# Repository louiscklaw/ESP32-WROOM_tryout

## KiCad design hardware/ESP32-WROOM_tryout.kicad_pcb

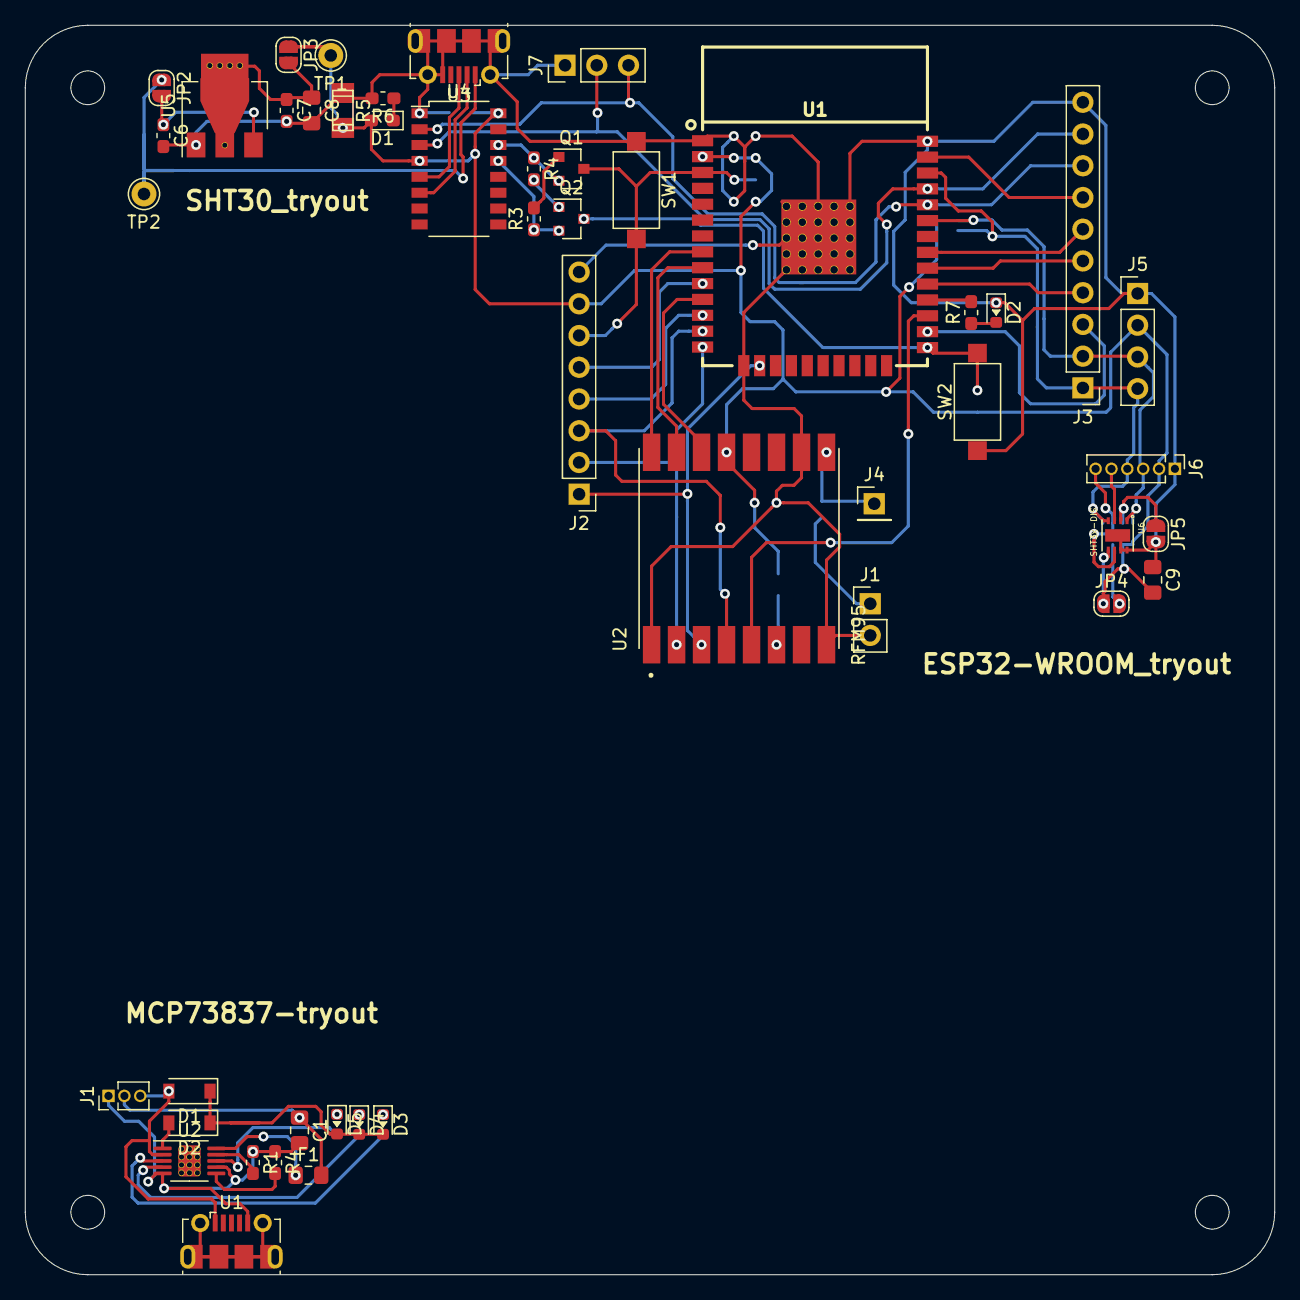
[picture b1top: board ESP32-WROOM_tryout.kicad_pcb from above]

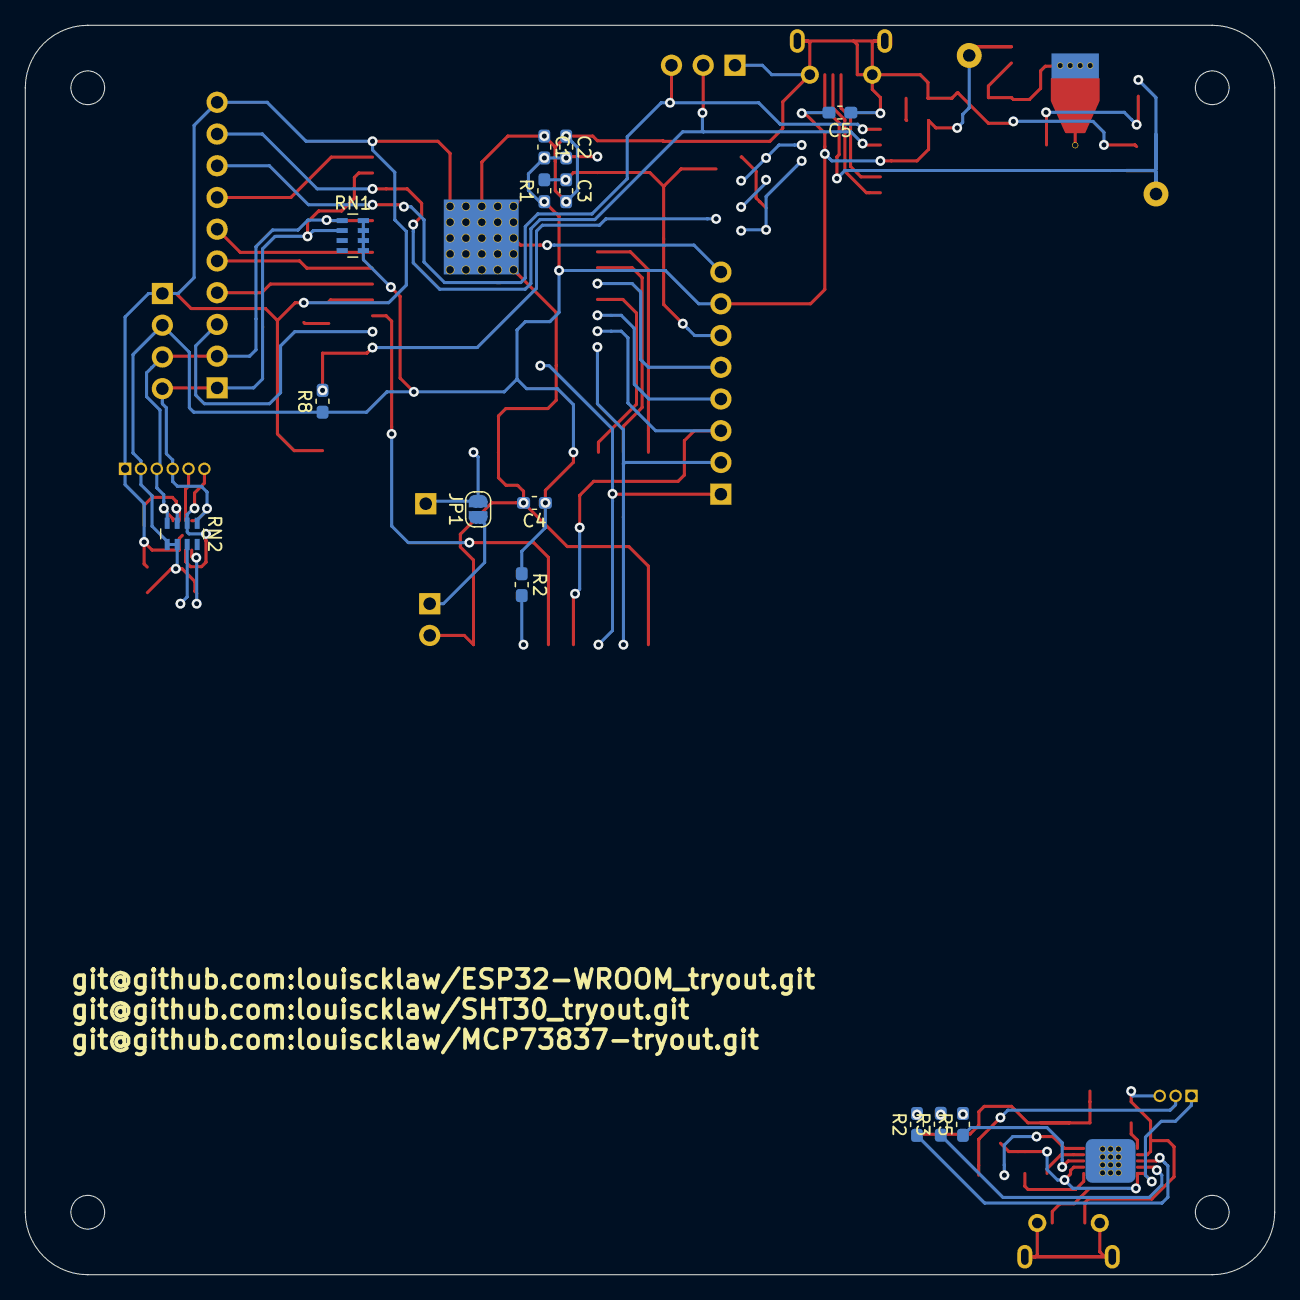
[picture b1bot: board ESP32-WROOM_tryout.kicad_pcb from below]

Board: 2 copper layers, 100.0 x 100.0 mm, 64 parts (14 on the bottom side), 51 nets.

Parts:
C1, C8: C106,0805; C_0805_2012Metric_Pad1.15x1.40mm_HandSolder
C1#2: C106,0603; C_0603_1608Metric_Pad1.05x0.95mm_HandSolder
C2, C3, C5, C6, C7: C104,0603; C_0603_1608Metric_Pad1.05x0.95mm_HandSolder
C4: C475,0603; C_0603_1608Metric_Pad1.05x0.95mm_HandSolder
C9: C104,0805; C_0805_2012Metric_Pad1.15x1.40mm_HandSolder
D1, D2: D_1N4148_T4; D_SOD-123
D1#2: LED_GREEN,0603; LED_0603_1608Metric_Pad1.05x0.95mm_HandSolder
D2#2: LED_BLUE,0603; LED_0603_1608Metric
D3: LED_ORANGE,0603; LED_0603_1608Metric
D4: LED_GREEN,0603; LED_0603_1608Metric
D5: LED_RED,0603; LED_0603_1608Metric
F1: Fuse_Small,0805; R_0805_2012Metric_Pad1.15x1.40mm_HandSolder
H1, H2, H3, H4: MOUNT_M2.5; MountingHole_2.7mm_M2.5,rpi_like
J1: OUT_HEADER; PinHeader_1x03_P1.27mm_Vertical
J1#2: ANT; PinHeader_1x02_P2.54mm_Vertical
J2: HEADER1; PinHeader_1x08_P2.54mm_Vertical
J3: HEADER2; PinHeader_1x10_P2.54mm_Vertical
J4: ANT; PinHeader_1x01_P2.54mm_Vertical
J5: I2C_HEADER; PinHeader_1x04_P2.54mm_Vertical
J6: SHT3x_HEADER; PinHeader_1x06_P1.27mm_Vertical
J7: TTL_DEBUG; PinHeader_1x03_P2.54mm_Vertical
JP1: ANT_EN; SolderJumper-2_P1.3mm_Open_RoundedPad1.0x1.5mm
JP2: 5V_EN; SolderJumper-2_P1.3mm_Open_RoundedPad1.0x1.5mm
JP3: 3V3_EN; SolderJumper-2_P1.3mm_Open_RoundedPad1.0x1.5mm
JP4: SolderJumper_2_Open_round; SolderJumper-2_P1.3mm_Open_RoundedPad1.0x1.5mm
JP5: J_ADDR; SolderJumper-2_P1.3mm_Open_RoundedPad1.0x1.5mm
Q1, Q2: 2N3904(1AM); MBT3904_1AM_SOT
R1, R1#2, R2, R3, R4, R7, R8: R103,0603; R_0603_1608Metric_Pad1.05x0.95mm_HandSolder
R2#2, R3#2, R4#2, R5: R122,0603; R_0603_1608Metric_Pad1.05x0.95mm_HandSolder
R5#2: VAR_3V3,1206; VAR_1206
R6: R102,0603; R_0603_1608Metric_Pad1.05x0.95mm_HandSolder
RN1: RN_473,0603; R_Array_Concave_4x0603
RN2: RN_472,0603; R_Array_Concave_4x0603
SW1, SW2: SW_RESET,2_leg,SMD; SW_SPST_CK_RS282G05A3
TP1: TP_3V3; Pin_D1.0mm_L10.0mm
TP2: TP_5V; Pin_D1.0mm_L10.0mm
U1, U3: USB_Micro; USB_Micro-B_Molex-105017-0001
U1#2: ESP-WROOM-32NARROW
U2: MCP73837_MSOP10
U2#2: RFM95
U4: CH340C
U5: AMS1117-3.3; AMS1117_SOT-223
U6: SHT3x-DIS

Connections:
+3V3: C1#2.2, C2.2, C4.1, C5.2, C9.2, D1#2.2, J2.7, J5.2, J6.2, JP3.1, JP4.1, R1.1, R2.1, R5#2.1, R8.1, RN1.5, RN1.6, RN1.7, RN1.8, RN2.5, RN2.6, TP1.1, U1#2.2, U2#2.13, U4.4, U4.16, U6.5
+5V: D1.2, J1.3, JP2.1, TP2.1, U1.1, U2.2, U3.1
/0: Q2.3, R8.2, SW2.2, U1#2.25
/ANT: J4.1, JP1.2, U2#2.9
/IO4: J3.3, U1#2.26
/IO5: J3.4, U1#2.29
/IO17: R7.2, U1#2.28
/IO18: J3.5, U1#2.30
/IO19: J3.6, U1#2.31
/IO23: J3.7, U1#2.37
/IO25: J2.5, U1#2.10
/IO27: J2.4, U1#2.12
/MISO: J2.2, U1#2.14, U2#2.2
/MOSI: J2.1, U1#2.16, U2#2.3
/RESET: C3.1, J2.6, Q1.3, R1.2, SW1.2, U1#2.3
/RFM95HW/RFM_RST: R2.2, U2#2.6
/RFM_CS: U1#2.27, U2#2.5
/RFM_DIO_32: U1#2.8, U2#2.16
/RFM_DIO_33: U1#2.9, U2#2.15
/RFM_INT_26: U1#2.11, U2#2.14
/RXI: J3.8, J7.3, U1#2.34, U4.2
/SCK: J2.3, U1#2.13, U2#2.4
/SCL: J3.1, J5.4, J6.4, RN1.2, RN2.1, U1#2.36, U6.4
/SDA: J3.2, J5.3, J6.3, RN1.1, RN2.4, U1#2.33, U6.1
/SHT3X/ADDR: JP5.1, RN2.3, U6.2
/SHT3X/ALERT: J6.5, U6.3
/SHT3X/NRST: J6.6, RN2.2, U6.6
/TXO: J3.9, J7.2, U1#2.35, U4.3
/auto_reset/DTR: Q2.2, R3.1, U4.13
/auto_reset/RTS: Q1.2, R4.1, U4.14
GND: C1.2, C1#2.1, C2.1, C3.2, C4.2, C5.1, C6.2, C7.2, C8.2, C9.1, D2#2.1, J1.1, J1#2.2, J2.8, J3.10, J5.1, J6.1, J7.1, JP5.2, R1#2.1, R4#2.1, R5#2.2, R6.2, SW1.1, SW2.1, U1.5, U1.6, U1.7, U1.8, U1.9, U1#2.1, U1#2.15, U1#2.38, U1#2.39, U2.5, U2.7, U2#2.1, U2#2.8, U2#2.10, U3.5, U3.6, U3.7, U3.8, U3.9, U4.1, U5.1, U6.7, U6.8, U6.PAD
unnamed: C6.1, JP2.2, U5.3
unnamed: C7.1, C8.1, JP3.2, U5.2
unnamed: D1.1, D1#2.1, D2.1, D3.2, D4.2, D5.2, R6.1
unnamed: D2.2, D2#2.2, R7.1, U2.1
unnamed: D3.1, R2#2.2
unnamed: D4.1, R3#2.2
unnamed: D5.1, R5.2
unnamed: F1.1, U2.10
unnamed: J1#2.1, JP1.1
unnamed: JP4.2, RN2.7, RN2.8
unnamed: Q1.1, R3.2
unnamed: Q2.1, R4.2
unnamed: R1#2.2, U2.9
unnamed: R2#2.1, U2.3
unnamed: R3#2.1, U2.4
unnamed: R4#2.2, U2.6
unnamed: R5.1, U2.8
unnamed: U3.2, U4.6
unnamed: U3.3, U4.5
Vout: C1.1, F1.2, J1.2

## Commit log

2019-06-14 update,
2019-06-14 update for DRC,
2019-06-17 in the middle,
2020-05-05 ci: init travis build config,
2020-05-05 ci: init travis token,
